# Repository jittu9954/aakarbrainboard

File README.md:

# AAKAR BRAINBOARD

Aakar Brainboard v2 is a modular CNC controller board based on LPC1768 Cortex-M3 chip. Due to its modular design it allows easier upgrades as per requirements and easy replacement if there is any broken part. It runs on open source Smoothie modular firmware and is targeted at 3D Printers, Laser cutters, CNC Mills, Pick and Place and other small or Mid size CNC machines.

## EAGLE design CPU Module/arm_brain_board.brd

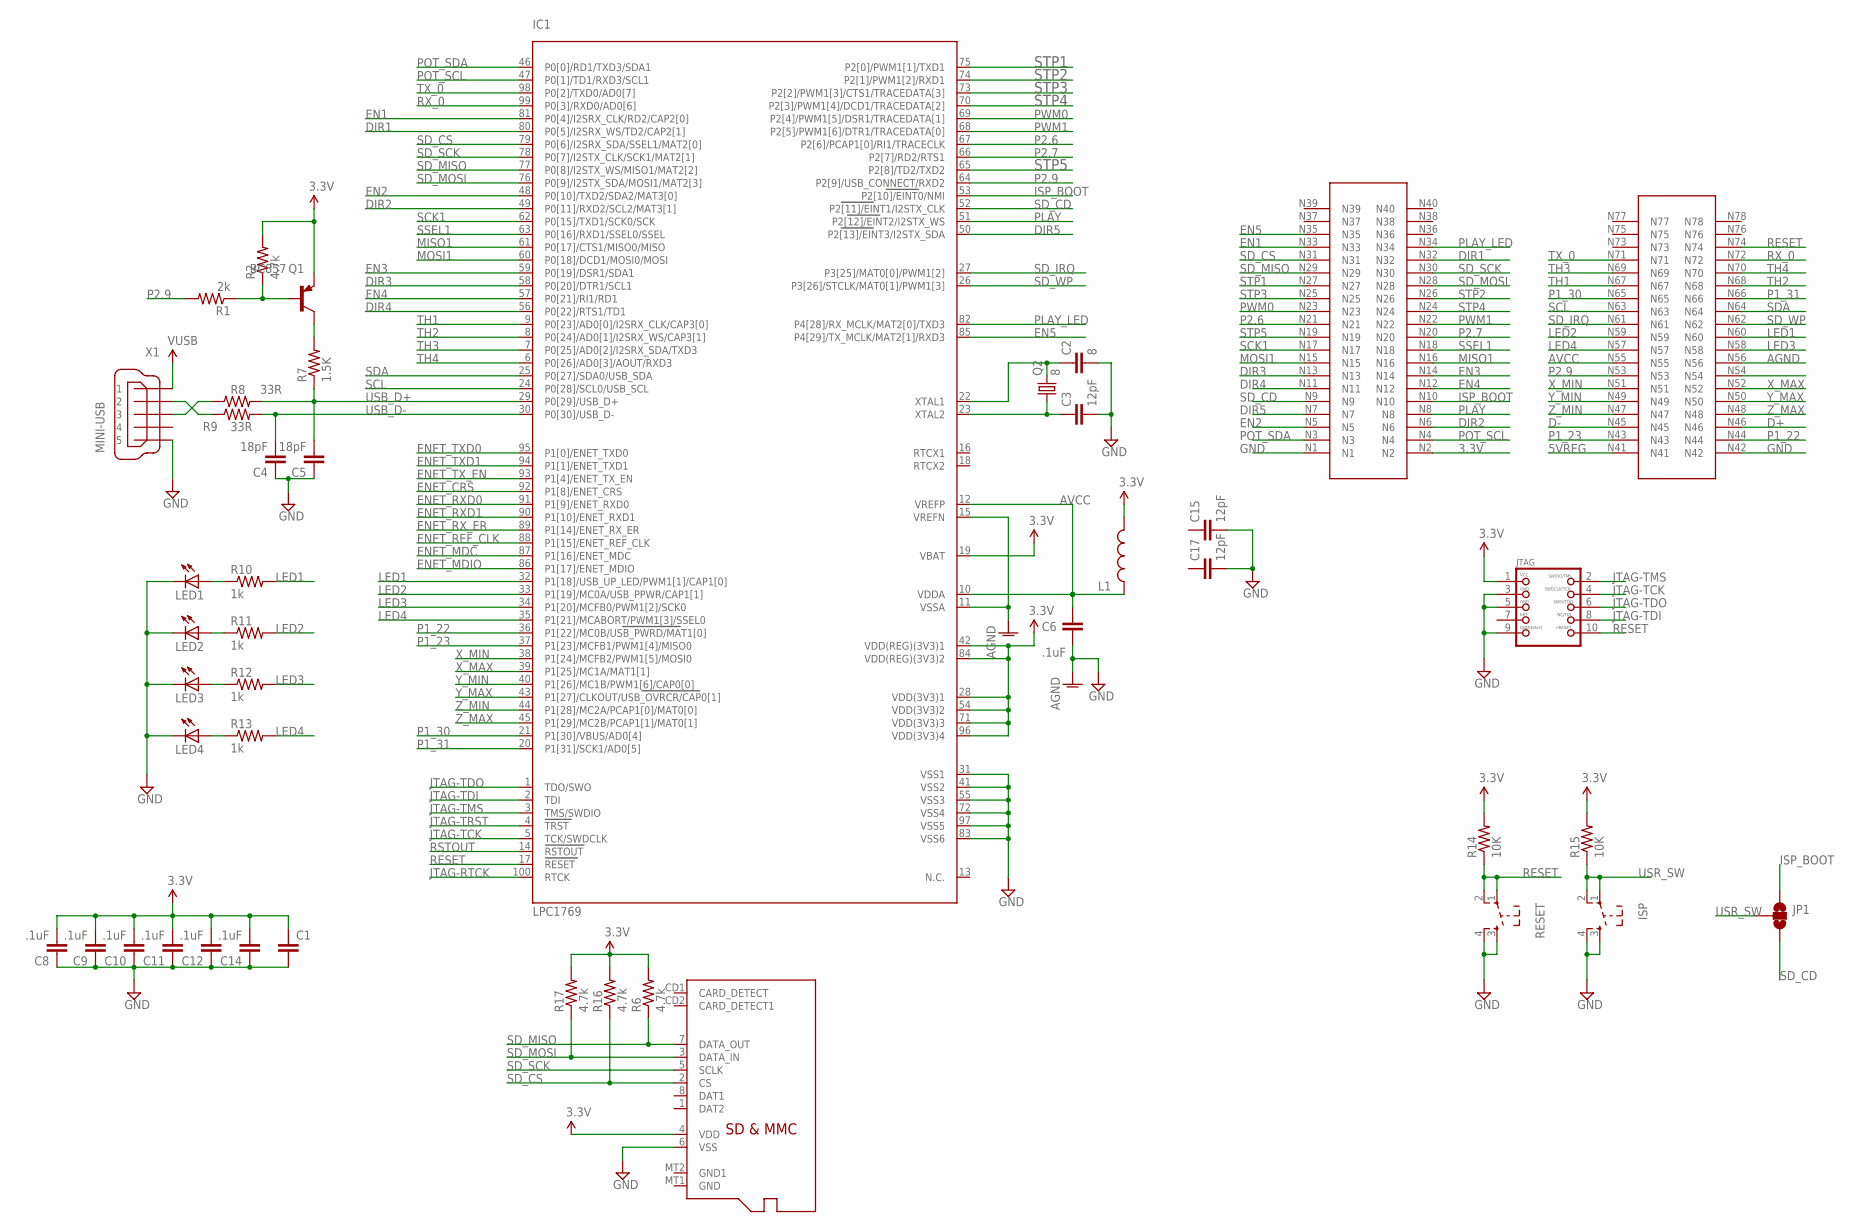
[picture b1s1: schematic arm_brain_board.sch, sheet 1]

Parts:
C1: CAP0603-CAP; 0603-CAP
C2: 8; 0603-CAP
C3, C15, C17: 12pF; 0603-CAP
C4: 18pF; 0603-CAP
C5: 18pF; C0603
C6, C8, C9, C10, C11, C12, C14: .1uF; 0603-CAP
IC1: LPC1769; LQFP100
ISP: SW_TACT_4P; SW_TACT_SMALL
JP1: SOLDERJUMPER_2WAYPASTE2&3; SJ_3_PASTE2&3
JTAG: JTAG-CORTEXM3; 2X05_1.27MM_SMT
L1: INDUCTOR0603; 0603
LED1, LED2, LED3, LED4: LEDCHIP-LED0603; CHIP-LED0603
MICROSD: MICROSD
Q1: BC857; SOT23-BEC
Q2: 8; HC49/S
R1: 2k; 0603-RES
R2: 4.7k; 0603-RES
R6, R16, R17: 4.7k; 0805
R7: 1.5K; 0603-RES
R8, R9: 33R; 0805
R10, R11, R12, R13: 1k; 0603-RES
R14, R15: 10K; 0603-RES
RESET: SW_TACT_4P; SW_TACT_SMALL
U$1: CPU_HEADER; CPU_BOARD
X1: MINI-USB; 32005-400

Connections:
3.3V: C1.1, C8.2, C9.2, C10.2, C11.2, C12.2, C14.2, IC1.19 (VBAT), IC1.28 (VDD(3V3)1), IC1.42 (VDD(REG)(3V3)1), IC1.54 (VDD(3V3)2), IC1.71 (VDD(3V3)3), IC1.84 (VDD(REG)(3V3)2), IC1.96 (VDD(3V3)4), JTAG.1, L1.2, MICROSD.4 (VDD), Q1.E, R2.2, R6.2, R14.2, R15.2, R16.2, R17.2, U$1.N2; also elsewhere on the board
5VREG: U$1.N41; also elsewhere on the board
AGND: C6.2, IC1.11 (VSSA), IC1.15 (VREFN), U$1.N56
AVCC: C6.1, IC1.10 (VDDA), IC1.12 (VREFP), L1.1, U$1.N55
D+: R8.1, U$1.N46, X1.3
D-: R9.1, U$1.N45, X1.2
DIR1: IC1.80 (P0[5]/I2SRX_WS/TD2/CAP2[1]), U$1.N32
DIR2: IC1.49 (P0[11]/RXD2/SCL2/MAT3[1]), U$1.N6
DIR3: IC1.58 (P0[20]/DTR1/SCL1), U$1.N13
DIR4: IC1.56 (P0[22]/RTS1/TD1), U$1.N11
DIR5: IC1.50 (P2[13]/EINT3/I2STX_SDA), U$1.N7
EN1: IC1.81 (P0[4]/I2SRX_CLK/RD2/CAP2[0]), U$1.N33
EN2: IC1.48 (P0[10]/TXD2/SDA2/MAT3[0]), U$1.N5
EN3: IC1.59 (P0[19]/DSR1/SDA1), U$1.N14
EN4: IC1.57 (P0[21]/RI1/RD1), U$1.N12
EN5: IC1.85 (P4[29]/TX_MCLK/MAT2[1]/RXD3), U$1.N35
ENET_CRS: IC1.92 (P1[8]/ENET_CRS); also elsewhere on the board
ENET_MDC: IC1.87 (P1[16]/ENET_MDC); also elsewhere on the board
ENET_MDIO: IC1.86 (P1[17]/ENET_MDIO); also elsewhere on the board
ENET_REF_CLK: IC1.88 (P1[15]/ENET_REF_CLK); also elsewhere on the board
ENET_RXD0: IC1.91 (P1[9]/ENET_RXD0); also elsewhere on the board
ENET_RXD1: IC1.90 (P1[10]/ENET_RXD1); also elsewhere on the board
ENET_RX_ER: IC1.89 (P1[14]/ENET_RX_ER); also elsewhere on the board
ENET_TXD0: IC1.95 (P1[0]/ENET_TXD0); also elsewhere on the board
ENET_TXD1: IC1.94 (P1[1]/ENET_TXD1); also elsewhere on the board
ENET_TX_EN: IC1.93 (P1[4]/ENET_TX_EN); also elsewhere on the board
GND: C1.2, C2.2, C3.2, C4.1, C5.1, C8.1, C9.1, C10.1, C11.1, C12.1, C14.1, C15.2, C17.2, IC1.31 (VSS1), IC1.41 (VSS2), IC1.55 (VSS3), IC1.72 (VSS4), IC1.83 (VSS6), IC1.97 (VSS5), ISP.3, ISP.4, JTAG.3, JTAG.5, JTAG.9, LED1.C, LED2.C, LED3.C, LED4.C, MICROSD.6 (VSS), RESET.3, RESET.4, U$1.N1, U$1.N42, X1.5; also elsewhere on the board
ISP_BOOT: IC1.53 (P2[10]/EINT0/NMI), JP1.1, U$1.N10
JTAG-RTCK: IC1.100 (RTCK)
JTAG-TCK: IC1.5 (TCK/SWDCLK), JTAG.4
JTAG-TDI: IC1.2 (TDI), JTAG.8
JTAG-TDO: IC1.1 (TDO/SWO), JTAG.6
JTAG-TMS: IC1.3 (TMS/SWDIO), JTAG.2
JTAG-TRST: IC1.4 (TRST)
LED1: IC1.32 (P1[18]/USB_UP_LED/PWM1[1]/CAP1[0]), R10.2, U$1.N60
LED2: IC1.33 (P1[19]/MC0A/USB_PPWR/CAP1[1]), R11.2, U$1.N59
LED3: IC1.34 (P1[20]/MCFB0/PWM1[2]/SCK0), R12.2, U$1.N58
LED4: IC1.35 (P1[21]/MCABORT/PWM1[3]/SSEL0), R13.2, U$1.N57
MISO1: IC1.61 (P0[17]/CTS1/MISO0/MISO), U$1.N16
MOSI1: IC1.60 (P0[18]/DCD1/MOSI0/MOSI), U$1.N15
unnamed: C2.1, IC1.22 (XTAL1), Q2.2
unnamed: C3.1, IC1.23 (XTAL2), Q2.1
unnamed: Q1.B, R1.1, R2.1
unnamed: Q1.C, R7.2
unnamed: LED4.A, R13.1
unnamed: LED3.A, R12.1
unnamed: LED2.A, R11.1
unnamed: LED1.A, R10.1
P1_22: IC1.36 (P1[22]/MC0B/USB_PWRD/MAT1[0]), U$1.N44
P1_23: IC1.37 (P1[23]/MCFB1/PWM1[4]/MISO0), U$1.N43
P1_30: IC1.21 (P1[30]/VBUS/AD0[4]), U$1.N65
P1_31: IC1.20 (P1[31]/SCK1/AD0[5]), U$1.N66
P2.6: IC1.67 (P2[6]/PCAP1[0]/RI1/TRACECLK), U$1.N21
P2.7: IC1.66 (P2[7]/RD2/RTS1), U$1.N20
P2.9: IC1.64 (P2[9]/USB_CONNECT/RXD2), R1.2, U$1.N53
PLAY: IC1.51 (P2[12]/EINT2/I2STX_WS), U$1.N8
PLAY_LED: IC1.82 (P4[28]/RX_MCLK/MAT2[0]/TXD3), U$1.N34
POT_SCL: IC1.47 (P0[1]/TD1/RXD3/SCL1), U$1.N4
POT_SDA: IC1.46 (P0[0]/RD1/TXD3/SDA1), U$1.N3
PWM0: IC1.69 (P2[4]/PWM1[5]/DSR1/TRACEDATA[1]), U$1.N23
PWM1: IC1.68 (P2[5]/PWM1[6]/DTR1/TRACEDATA[0]), U$1.N22
RESET: IC1.17 (RESET), JTAG.10, R14.1, RESET.1, RESET.2, U$1.N74
RSTOUT: IC1.14 (RSTOUT); also elsewhere on the board
RX_0: IC1.99 (P0[3]/RXD0/AD0[6]), U$1.N72
SCK1: IC1.62 (P0[15]/TXD1/SCK0/SCK), U$1.N17
SCL: IC1.24 (P0[28]/SCL0/USB_SCL), U$1.N63
SDA: IC1.25 (P0[27]/SDA0/USB_SDA), U$1.N64
SD_CD: IC1.52 (P2[11]/EINT1/I2STX_CLK), JP1.3, U$1.N9
SD_CS: IC1.79 (P0[6]/I2SRX_SDA/SSEL1/MAT2[0]), MICROSD.2 (CS), R16.1, U$1.N31
SD_IRQ: IC1.27 (P3[25]/MAT0[0]/PWM1[2]), U$1.N61
SD_MISO: IC1.77 (P0[8]/I2STX_WS/MISO1/MAT2[2]), MICROSD.7 (DATA_OUT), R6.1, U$1.N29
SD_MOSI: IC1.76 (P0[9]/I2STX_SDA/MOSI1/MAT2[3]), MICROSD.3 (DATA_IN), R17.1, U$1.N28
SD_SCK: IC1.78 (P0[7]/I2STX_CLK/SCK1/MAT2[1]), MICROSD.5 (SCLK), U$1.N30
SD_WP: IC1.26 (P3[26]/STCLK/MAT0[1]/PWM1[3]), U$1.N62
SSEL1: IC1.63 (P0[16]/RXD1/SSEL0/SSEL), U$1.N18
STP1: IC1.75 (P2[0]/PWM1[1]/TXD1), U$1.N27
STP2: IC1.74 (P2[1]/PWM1[2]/RXD1), U$1.N26
STP3: IC1.73 (P2[2]/PWM1[3]/CTS1/TRACEDATA[3]), U$1.N25
STP4: IC1.70 (P2[3]/PWM1[4]/DCD1/TRACEDATA[2]), U$1.N24
STP5: IC1.65 (P2[8]/TD2/TXD2), U$1.N19
TH1: IC1.9 (P0[23]/AD0[0]/I2SRX_CLK/CAP3[0]), U$1.N67
TH2: IC1.8 (P0[24]/AD0[1]/I2SRX_WS/CAP3[1]), U$1.N68
TH3: IC1.7 (P0[25]/AD0[2]/I2SRX_SDA/TXD3), U$1.N69
TH4: IC1.6 (P0[26]/AD0[3]/AOUT/RXD3), U$1.N70
TX_0: IC1.98 (P0[2]/TXD0/AD0[7]), U$1.N71
USB_D+: C5.2, IC1.29 (P0[29]/USB_D+), R7.1, R8.2
USB_D-: C4.2, IC1.30 (P0[30]/USB_D-), R9.2
USR_SW: ISP.1, ISP.2, JP1.2, R15.1
VUSB: X1.1; also elsewhere on the board
X_MAX: IC1.39 (P1[25]/MC1A/MAT1[1]), U$1.N52
X_MIN: IC1.38 (P1[24]/MCFB2/PWM1[5]/MOSI0), U$1.N51
Y_MAX: IC1.43 (P1[27]/CLKOUT/USB_OVRCR/CAP0[1]), U$1.N50
Y_MIN: IC1.40 (P1[26]/MC1B/PWM1[6]/CAP0[0]), U$1.N49
Z_MAX: IC1.45 (P1[29]/MC2B/PCAP1[1]/MAT0[1]), U$1.N48
Z_MIN: IC1.44 (P1[28]/MC2A/PCAP1[0]/MAT0[0]), U$1.N47

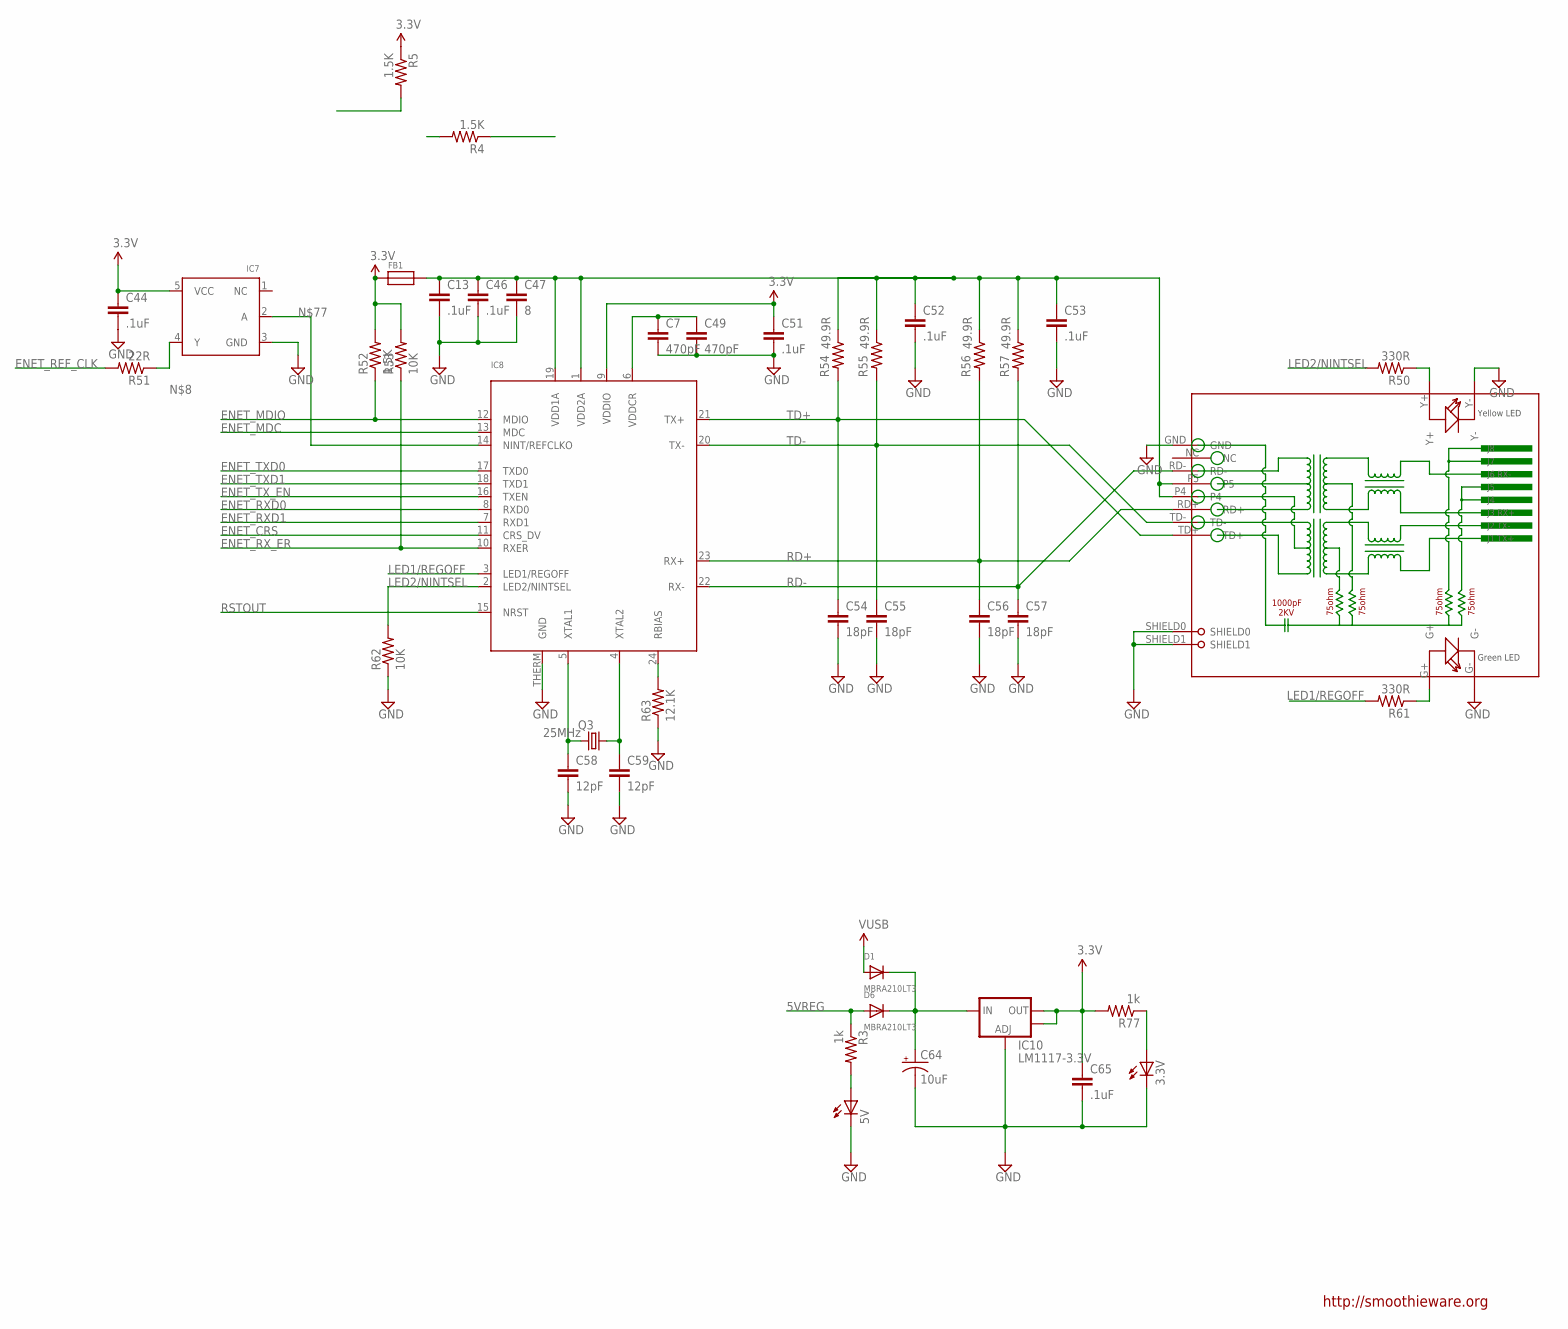
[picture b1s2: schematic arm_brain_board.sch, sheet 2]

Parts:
3.3V, 5V: LEDCHIP-LED0603; CHIP-LED0603
C7, C49: 470pF; 0603-CAP
C13, C44, C46, C51, C52, C53: .1uF; 0603-CAP
C47: 8; 0603-CAP
C54, C57: 18pF; 0805
C55, C56: 18pF; 0603-CAP
C58, C59: 12pF; 0603-CAP
C64: 10uF; EIA3216
C65: .1uF; 0805
D1, D6: MBRA210LT3; SOD-123
FB1: FERRITE; 0603
IC7: 74LVC1G04; SOT23-5
IC8: LAN8720; QFN24_4MM
IC10: LM1117-3.3V; SOT223
Q3: 25MHz; HC49/S
R3, R77: 1k; 0603-RES
R4, R5, R52: 1.5K; 0603-RES
R50, R61: 330R; R0603
R51: 22R; 0603-RES
R53, R62: 10K; 0603-RES
R54, R57: 49.9R; 0603-RES
R55, R56: 49.9R; 0805
R63: 12.1K; 0603-RES
RJ1: HR911105A

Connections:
3.3V: C44.1, C51.1, C65.1, FB1.1, IC7.5 (VCC), IC8.9 (VDDIO), IC10.2 (OUT), IC10.4 (OUT), R5.1, R52.2, R53.2, R77.2; also elsewhere on the board
5VREG: D6.A, R3.1; also elsewhere on the board
ENET_CRS: IC8.11 (CRS_DV); also elsewhere on the board
ENET_MDC: IC8.13 (MDC); also elsewhere on the board
ENET_MDIO: IC8.12 (MDIO), R52.1; also elsewhere on the board
ENET_REF_CLK: R51.2; also elsewhere on the board
ENET_RXD0: IC8.8 (RXD0); also elsewhere on the board
ENET_RXD1: IC8.7 (RXD1); also elsewhere on the board
ENET_RX_ER: IC8.10 (RXER), R53.1; also elsewhere on the board
ENET_TXD0: IC8.17 (TXD0); also elsewhere on the board
ENET_TXD1: IC8.18 (TXD1); also elsewhere on the board
ENET_TX_EN: IC8.16 (TXEN); also elsewhere on the board
GND: 3.3V.C, 5V.C, C7.2, C13.2, C44.2, C46.2, C47.2, C49.2, C51.2, C52.2, C53.2, C54.2, C55.2, C56.2, C57.2, C58.2, C59.2, C64.C (-), C65.2, IC7.3 (GND), IC8.THERM (GND), IC10.1 (ADJ), R62.1, R63.1, RJ1.G-, RJ1.GND, RJ1.SHIELD0, RJ1.SHIELD1, RJ1.Y-; also elsewhere on the board
LED1/REGOFF: IC8.3 (LED1/REGOFF), R61.2
LED2/NINTSEL: IC8.2 (LED2/NINTSEL), R50.2, R62.2
unnamed: C64.A (+), D1.C, D6.C, IC10.3 (IN)
unnamed: R50.1, RJ1.Y+
unnamed: R61.1, RJ1.G+
unnamed: IC7.4 (Y), R5.2, R51.1
unnamed: 5V.A, R3.2
unnamed: C13.1, C46.1, C47.1, C52.1, C53.1, FB1.2, IC8.1 (VDD2A), IC8.19 (VDD1A), R54.1, R55.1, R56.1, R57.1, RJ1.P4, RJ1.P5
unnamed: C59.1, IC8.4 (XTAL2), Q3.1
unnamed: C58.1, IC8.5 (XTAL1), Q3.2
unnamed: IC8.24 (RBIAS), R63.2
unnamed: IC7.2 (A), IC8.14 (NINT/REFCLKO), R4.1
unnamed: 3.3V.A, R77.1
unnamed: C7.1, C49.1, IC8.6 (VDDCR)
RD+: C56.1, IC8.23 (RX+), R56.2, RJ1.RD+
RD-: C57.1, IC8.22 (RX-), R57.2, RJ1.RD-
RSTOUT: IC8.15 (NRST); also elsewhere on the board
TD+: C54.1, IC8.21 (TX+), R54.2, RJ1.TD+
TD-: C55.1, IC8.20 (TX-), R55.2, RJ1.TD-
VUSB: D1.A; also elsewhere on the board

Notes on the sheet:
http://smoothieware.org

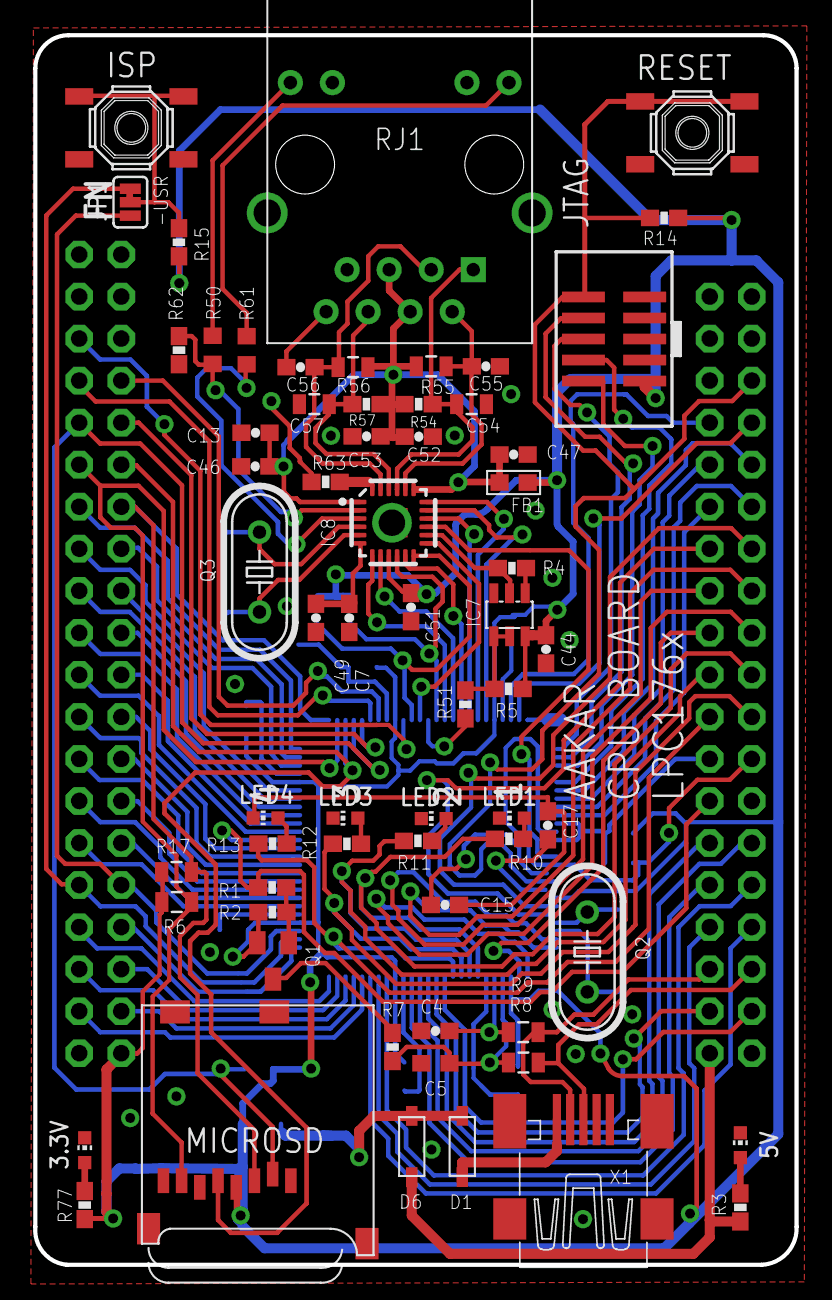
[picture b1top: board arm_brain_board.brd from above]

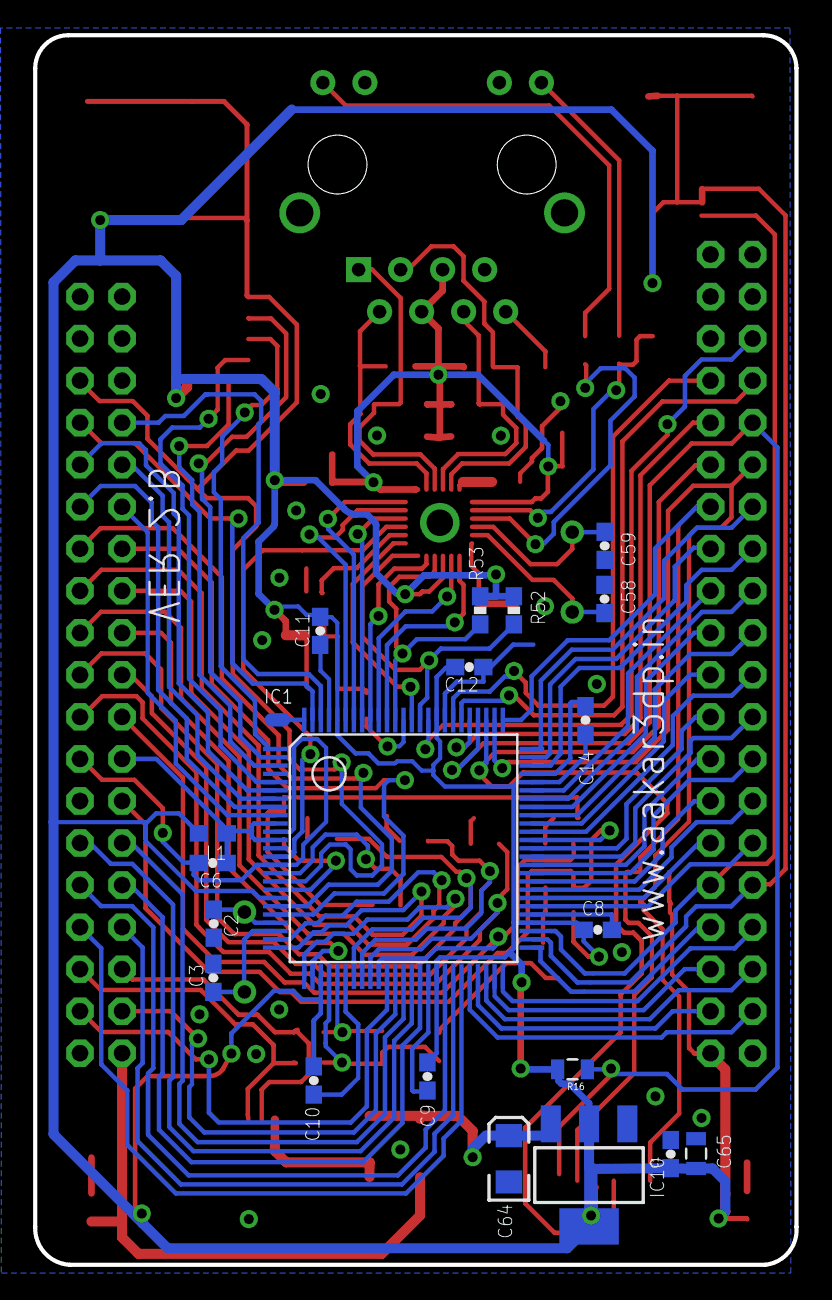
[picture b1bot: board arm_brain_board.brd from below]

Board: 2 copper layers, 46.0 x 74.3 mm, 85 parts (20 on the bottom side), 111 nets.

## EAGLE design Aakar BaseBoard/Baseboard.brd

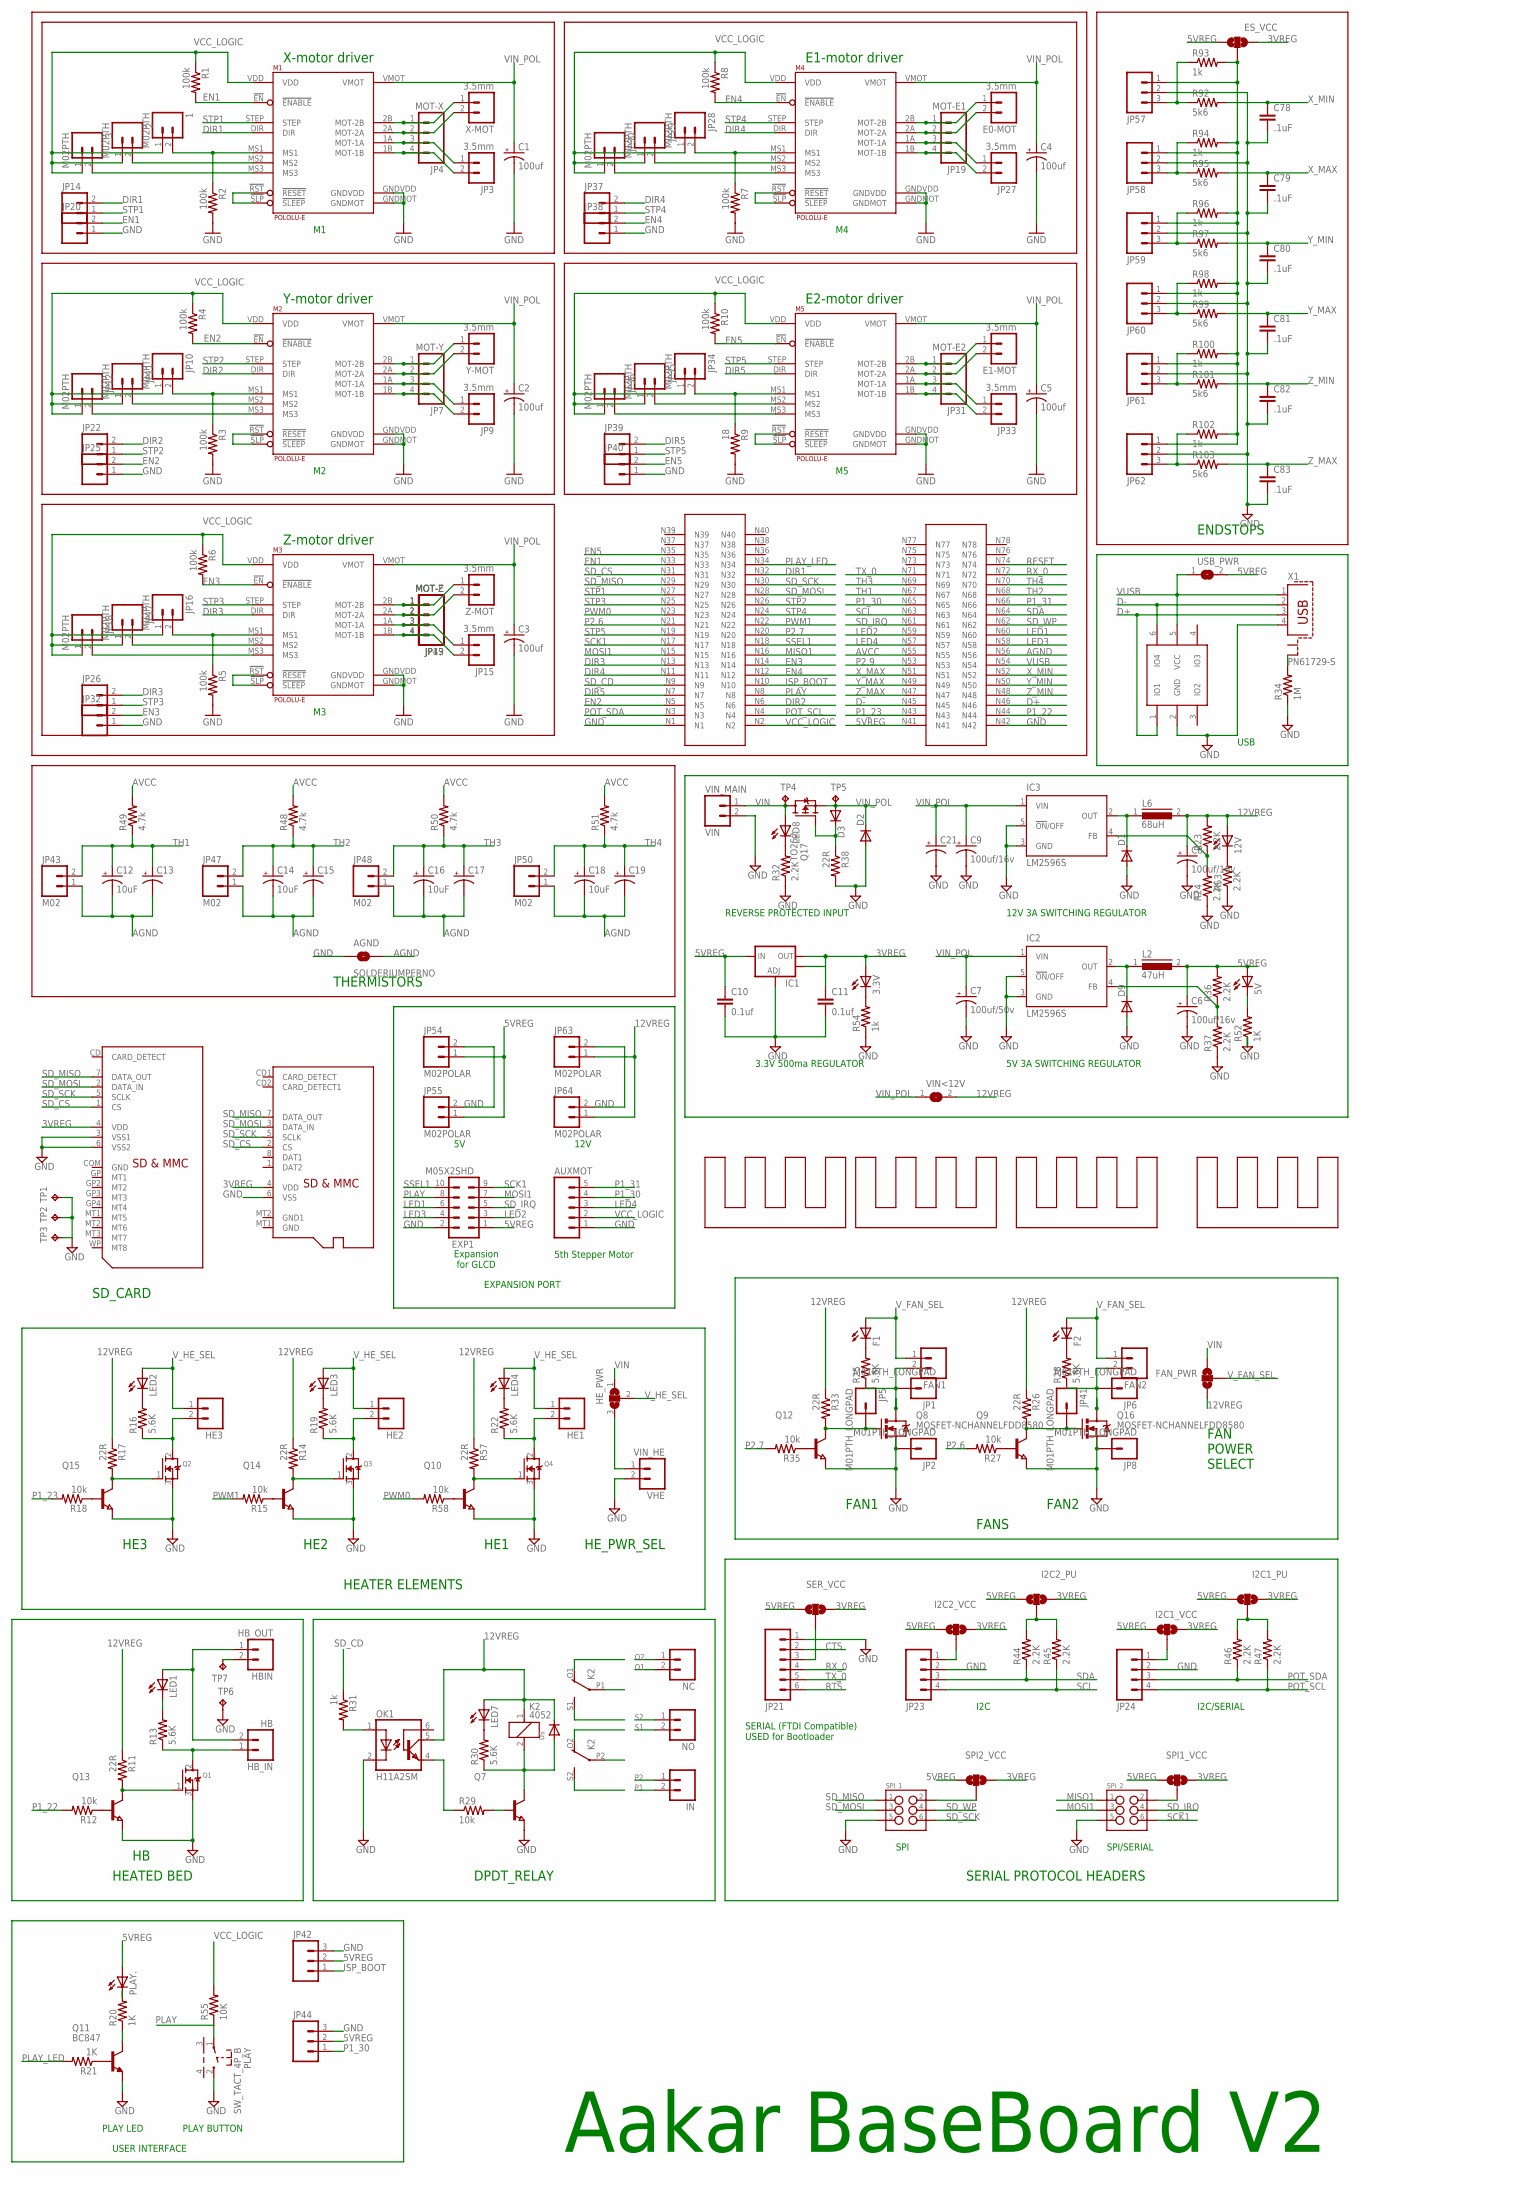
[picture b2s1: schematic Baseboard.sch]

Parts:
1, 2, 3: M02PTH; 1X02
3.3V, 5V, 12V: LEDCHIP-LED0603; CHIP-LED0603
AGND: SOLDERJUMPERNO; SJ_2S-NO
AUXMOT: M05PTH_LONGPADS; 1X05_LONGPADS
C1, C2, C3, C4, C5: 100uf; CPOL-RADIAL-100UF-25V
C6, C8, C9: 100uf/16v; E3,5-8
C7: 100uf/50v; E5-10,5
C10, C11: 0.1uf; 0805
C12, C14, C16, C18: 10uF; EIA3216
C13, C15, C17, C19: CAP_POLPTH2; CPOL-RADIAL-10UF-25V
C21: CPOL-USE2.5-7; E2,5-7
C78, C79, C80, C81, C82, C83: .1uF; 0805
D1, D9: DIODE-SMC; SMC
D2, D3: DIODE-GF1; GF1
D5: DIODESMA; SMADIODE
E0-MOT, E1-MOT: 3.5mm; SCREWTERMINAL-3.5MM-2_LOCK
ES_VCC: SOLDERJUMPER_2WAYS; SJ_3
EXP1: M05X2SHD; 2X5-SHROUDED
F1, F2: LEDCHIP-LED0603; CHIP-LED0603
FAN1, FAN2: M025MM; SCREWTERMINAL-5MM-2
FAN_PWR: SOLDERJUMPER_2WAYT; SJ_2
HB: HB_IN; SCREWTERMINAL-5MM-2
HBIN: HB_OUT; SCREWTERMINAL-5MM-2
HE1, HE2, HE3: M025MM; SCREWTERMINAL-5MM-2
HE_PWR: SJ2WW; SJ_2W
I2C1_PU, I2C1_VCC, I2C2_PU, I2C2_VCC: SOLDERJUMPER_2WAYPASTE1&2; SJ_3_PASTE1&2
IC1: V_REG_LM1117SOT223; SOT223
IC2, IC3: LM2596S; TO263-5
IN: M025MM; SCREWTERMINAL-5MM-2
JP1, JP2, JP5, JP6, JP8, JP41: M01PTH_LONGPAD; 1X01_LONGPAD
JP3, JP9, JP15, JP27, JP33: 3.5mm; SCREWTERMINAL-3.5MM-2_LOCK
JP4: MOT-X; MOLEX-1X4
JP7: MOT-Y; MOLEX-1X4
JP10, JP11, JP12, JP16, JP17, JP18, JP28, JP29, JP30, JP34, JP35, JP36: M02PTH; 1X02
JP13: MOT-E; MOLEX-1X4
JP14, JP20, JP22, JP25, JP26, JP32, JP37, JP38, JP39, JP40: M02POGO_PIN_HOLES_ONLY; 1X02_PP_HOLES_ONLY
JP19: MOT-E1; MOLEX-1X4
JP21: M06POLAR; MOLEX-1X6
JP23, JP24: M04POLAR; MOLEX-1X4
JP31: MOT-E2; MOLEX-1X4
JP42, JP44, JP57, JP58, JP59, JP60, JP61, JP62: M03POLAR; MOLEX-1X3
JP43, JP47, JP48, JP50: M02; MOLEX-1X2_LOCK
JP49: MOT-Z; MOLEX-1X4
JP54, JP55, JP63, JP64: M02POLAR; MOLEX-1X2
K2: 4052; F4052
L2: 47uH; A26GFC
L6: 68uH; A26GFC
LED1, LED2, LED3, LED4, LED7, LED8: LEDCHIP-LED0603; CHIP-LED0603
M1, M2, M3, M4, M5: POLOLU-E; POLOLU-ALLEGRO-PTH
NC: M025MM; SCREWTERMINAL-5MM-2
NO: M025MM; SCREWTERMINAL-5MM-2
OK1: H11A2SM; DIL6-SMD
PLAY: SW_TACT_4P_B; SW_TACT_STANDARD_RIGHT_ANGLE
PLAY.: LED5MM
Q1, Q2, Q3, Q4: MOSFET-NGDS_TO220V; TO220V
Q7, Q9, Q10, Q12, Q13, Q14, Q15: NPN-TRANSISTOR_SOT23; SOT23
Q8, Q16: MOSFET-NCHANNELFDD8580; DPAK
Q11: BC847; SOT23
Q17: TO252
R1, R2, R3, R4, R5, R6, R7, R8, R10: 100k; 0603-RES
R9: 18; 0603-RES
R11, R14, R17, R26, R33, R38, R57: 22R; 0603-RES
R12, R15, R18, R27, R29, R35, R58: 10k; 0603-RES
R13, R16, R19, R22, R25, R28, R30: 5.6K; 0603-RES
R20, R21, R52: 1K; 0603-RES
R23, R24, R32, R36, R37, R44, R45, R46, R47, R53: 2.2K; 0603-RES
R31, R54, R93, R94, R96, R98, R100, R102: 1k; 0603-RES
R34: 1M; 0805
R48, R49, R50, R51: 4.7k; 0603-RES
R55: 10K; 0603-RES
R92, R95, R97, R99, R101, R103: 5k6; 0603-RES
SER_VCC: SOLDERJUMPER_2WAYPASTE1&2; SJ_3_PASTE1&2
SPI1_VCC, SPI2_VCC: SOLDERJUMPER_2WAYPASTE1&2; SJ_3_PASTE1&2
SPI_1, SPI_2: M03X2NO_SILK; 2X3-NS
TP1, TP2, TP3: TPTP15SQ; TP15SQ
TP4, TP5: TPPAD1-13; P1-13
TP6, TP7: TPPAD1-17Y; P1-17Y
U$1, U$8, U$10, U$12: HEATSINK; HEAT_TO
U$2: MICROSD
U$4: CPU_HEADER; CPU_BOARD
U$9: ESD; SOT23-6
U$11: SD_MMC
USB_PWR: SJ
VHE: VIN_HE; SCREWTERMINAL-5MM-2
VIN: VIN_MAIN; SCREWTERMINAL-5MM-2
VIN<12V: SJ
X1: PN61729-S
X-MOT: 3.5mm; SCREWTERMINAL-3.5MM-2_LOCK
Y-MOT: 3.5mm; SCREWTERMINAL-3.5MM-2_LOCK
Z-MOT: 3.5mm; SCREWTERMINAL-3.5MM-2_LOCK

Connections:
3VREG: 3.3V.A, C11.1, ES_VCC.3, I2C1_PU.3, I2C1_VCC.3, I2C2_PU.3, I2C2_VCC.3, IC1.2 (OUT), IC1.4 (OUT), SER_VCC.3, SPI1_VCC.3, SPI2_VCC.3, U$2.4 (VDD), U$11.4 (VDD)
5VREG: 5V.A, C6.+, C10.1, ES_VCC.1, EXP1.1, I2C1_PU.1, I2C1_VCC.1, I2C2_PU.1, I2C2_VCC.1, IC1.3 (IN), JP42.2, JP44.2, JP54.1, JP55.1, L2.2, PLAY..A, R36.2, SER_VCC.1, SPI1_VCC.1, SPI2_VCC.1, U$4.N41, USB_PWR.2
12VREG: 12V.A, C8.+, D5.C, FAN_PWR.3, JP63.1, JP64.1, K2.1, L6.2, LED7.A, OK1.5 (COL), R11.1, R14.1, R17.1, R23.2, R26.1, R33.1, R57.1, VIN<12V.2
AGND: AGND.2, C12.C (-), C13.2 (-), C14.C (-), C15.2 (-), C16.C (-), C17.2 (-), C18.C (-), C19.2 (-), JP43.1, JP47.1, JP48.1, JP50.1, U$4.N56
AVCC: R48.2, R49.2, R50.2, R51.2, U$4.N55
CTS: JP21.2
D+: U$4.N46, U$9.1 (IO1), X1.3
D-: U$4.N45, U$9.6 (IO4), X1.2
DIR1: JP14.2, M1.DIR, U$4.N32
DIR2: JP22.2, M2.DIR, U$4.N6
DIR3: JP26.2, M3.DIR, U$4.N13
DIR4: JP37.2, M4.DIR, U$4.N11
DIR5: JP39.2, M5.DIR, U$4.N7
E-MOT-1A: JP3.1, JP4.3, M1.1A (MOT-1A)
E-MOT-1A1: JP7.3, JP9.1, M2.1A (MOT-1A)
E-MOT-1A2: JP13.3, JP15.1, JP49.3, M3.1A (MOT-1A)
E-MOT-1A3: JP19.3, JP27.1, M4.1A (MOT-1A)
E-MOT-1A4: JP31.3, JP33.1, M5.1A (MOT-1A)
E-MOT-1B: JP3.2, JP4.4, M1.1B (MOT-1B)
E-MOT-1B1: JP7.4, JP9.2, M2.1B (MOT-1B)
E-MOT-1B2: JP13.4, JP15.2, JP49.4, M3.1B (MOT-1B)
E-MOT-1B3: JP19.4, JP27.2, M4.1B (MOT-1B)
E-MOT-1B4: JP31.4, JP33.2, M5.1B (MOT-1B)
E-MOT-2A: JP4.2, M1.2A (MOT-2A), X-MOT.2
E-MOT-2A1: JP7.2, M2.2A (MOT-2A), Y-MOT.2
E-MOT-2A2: JP13.2, JP49.2, M3.2A (MOT-2A), Z-MOT.2
E-MOT-2A3: E0-MOT.2, JP19.2, M4.2A (MOT-2A)
E-MOT-2A4: E1-MOT.2, JP31.2, M5.2A (MOT-2A)
E-MOT-2B: JP4.1, M1.2B (MOT-2B), X-MOT.1
E-MOT-2B1: JP7.1, M2.2B (MOT-2B), Y-MOT.1
E-MOT-2B2: JP13.1, JP49.1, M3.2B (MOT-2B), Z-MOT.1
E-MOT-2B3: E0-MOT.1, JP19.1, M4.2B (MOT-2B)
E-MOT-2B4: E1-MOT.1, JP31.1, M5.2B (MOT-2B)
E-RESETSLEEP: M1.!RST (!RESET), M1.!SLP (!SLEEP)
E-RESETSLEEP1: M2.!RST (!RESET), M2.!SLP (!SLEEP)
E-RESETSLEEP2: M3.!RST (!RESET), M3.!SLP (!SLEEP)
E-RESETSLEEP3: M4.!RST (!RESET), M4.!SLP (!SLEEP)
E-RESETSLEEP4: M5.!RST (!RESET), M5.!SLP (!SLEEP)
EN1: JP20.2, M1.!EN (!ENABLE), R1.2, U$4.N33
EN2: JP25.2, M2.!EN (!ENABLE), R4.2, U$4.N5
EN3: JP32.2, M3.!EN (!ENABLE), R6.2, U$4.N14
EN4: JP38.2, M4.!EN (!ENABLE), R8.2, U$4.N12
EN5: JP40.2, M5.!EN (!ENABLE), R10.2, U$4.N35
GND: AGND.1, AUXMOT.1, C1.2 (-), C2.2 (-), C3.2 (-), C4.2 (-), C5.2 (-), C6.-, C7.-, C8.-, C9.-, C10.2, C11.2, C21.-, C78.2, C79.2, C80.2, C81.2, C82.2, C83.2, D1.A, D2.A, D9.A, EXP1.2, IC1.1 (ADJ), IC2.3 (GND), IC2.5 (!ON!/OFF), IC3.3 (GND), IC3.5 (!ON!/OFF), JP2.1, JP8.1, JP20.1, JP21.1, JP23.2, JP24.2, JP25.1, JP32.1, JP38.1, JP40.1, JP42.3, JP44.3, JP54.2, JP55.2, JP57.2, JP58.2, JP59.2, JP60.2, JP61.2, JP62.2, JP63.2, JP64.2, M1.GNDMOT, M1.GNDVDD, M2.GNDMOT, M2.GNDVDD, M3.GNDMOT, M3.GNDVDD, M4.GNDMOT, M4.GNDVDD, M5.GNDMOT, M5.GNDVDD, OK1.2 (C), PLAY.2, Q1.3 (S), Q2.3 (S), Q3.3 (S), Q4.3 (S), Q7.2 (E), Q8.3 (S), Q9.2 (E), Q10.2 (E), Q11.2 (E), Q12.2 (E), Q13.2 (E), Q14.2 (E), Q15.2 (E), Q16.3 (S), R2.2, R3.2, R5.2, R7.2, R9.2, R24.1, R32.1, R34.1, R37.1, R38.2, R52.1, R53.1, R54.1, SPI_1.5, SPI_2.5, TP1.TP, TP2.TP, TP3.TP, TP6.TP, U$2.6 (VSS), U$4.N1, U$4.N42, U$9.2 (GND), U$11.3 (VSS1), U$11.6 (VSS2), VHE.2, VIN.2, X1.4
ISP_BOOT: JP42.1, U$4.N10
LED1: EXP1.6, U$4.N60
LED2: EXP1.3, U$4.N59
LED3: EXP1.4, U$4.N58
LED4: AUXMOT.3, U$4.N57
MISO1: SPI_2.1, U$4.N16
MOSI1: EXP1.7, SPI_2.3, U$4.N15
unnamed: JP11.2, M2.MS2
unnamed: JP10.2, M2.MS1, R3.1
unnamed: JP12.2, M2.MS3
unnamed: JP17.2, M3.MS2
unnamed: JP16.2, M3.MS1, R5.1
unnamed: JP18.2, M3.MS3
unnamed: JP29.2, M4.MS2
unnamed: JP28.2, M4.MS1, R7.1
unnamed: JP30.2, M4.MS3
unnamed: JP35.2, M5.MS2
unnamed: JP34.2, M5.MS1, R9.1
unnamed: JP36.2, M5.MS3
unnamed: D1.C, IC3.2 (OUT), L6.1
unnamed: D9.C, IC2.2 (OUT), L2.1
unnamed: HB.1, Q1.2 (D), R13.1
unnamed: HBIN.2, TP7.TP
unnamed: HB.2, HBIN.1, LED1.A
unnamed: Q1.1 (G), Q13.3 (C), R11.2
unnamed: LED1.C, R13.2
unnamed: 2.2, M1.MS2
unnamed: 1.2, M1.MS1, R2.1
unnamed: 3.2, M1.MS3
unnamed: SPI1_VCC.2, SPI_2.2
unnamed: LED2.C, R16.2
unnamed: SPI2_VCC.2, SPI_1.2
unnamed: Q3.1 (G), Q14.3 (C), R14.2
unnamed: HE3.2, Q2.2 (D), R16.1
unnamed: F1.C, R25.2
unnamed: LED3.C, R19.2
unnamed: Q14.1 (B), R15.1
unnamed: HE2.2, Q3.2 (D), R19.1
unnamed: Q13.1 (B), R12.1
unnamed: LED4.C, R22.2
unnamed: Q11.1 (B), R21.1
unnamed: HE1.2, Q4.2 (D), R22.1
unnamed: 5V.C, R52.2
unnamed: Q2.1 (G), Q15.3 (C), R17.2
unnamed: FAN1.2, JP1.1, Q8.4 (D), R25.1
unnamed: 12V.C, R53.2
unnamed: F2.C, R28.2
unnamed: JP41.1, Q9.3 (C), Q16.1 (G), R26.2
unnamed: FAN2.2, JP6.1, Q16.4 (D), R28.1
unnamed: 3.3V.C, R54.2
unnamed: OK1.1 (A), R31.2
unnamed: OK1.4 (EMI), R29.1
unnamed: Q7.1 (B), R29.2
unnamed: Q15.1 (B), R18.1
unnamed: LED7.C, R30.2
unnamed: D5.A, K2.2, Q7.3 (C), R30.1
unnamed: LED8.C, R32.2
unnamed: JP5.1, Q8.1 (G), Q12.3 (C), R33.2
unnamed: IC2.4 (FB), R36.1, R37.2
unnamed: JP21.3, SER_VCC.2
unnamed: R34.2, X1.S2
unnamed: PLAY..K (C), R20.2
unnamed: Q12.1 (B), R35.1
unnamed: I2C2_VCC.2, JP23.1
unnamed: I2C2_PU.2, R44.2, R45.2
unnamed: I2C1_VCC.2, JP24.1
unnamed: I2C1_PU.2, R46.2, R47.2
unnamed: D3.C, Q17.1 (G), R38.1
unnamed: JP61.3, R100.1, R101.1
unnamed: JP59.3, R96.1, R97.1
unnamed: JP62.3, R102.1, R103.1
unnamed: Q9.1 (B), R27.1
unnamed: Q4.1 (G), Q10.3 (C), R57.2
unnamed: Q10.1 (B), R58.1
unnamed: IC3.4 (FB), R23.1, R24.2
unnamed: JP58.3, R94.1, R95.1
unnamed: ES_VCC.2, JP57.1, JP58.1, JP59.1, JP60.1, JP61.1, JP62.1, R93.2, R94.2, R96.2, R98.2, R100.2, R102.2
unnamed: JP60.3, R98.1, R99.1
unnamed: JP57.3, R92.1, R93.1
O1: K2.O1 (O), NC.2
O2: K2.O2 (O), NC.1
P1: IN.2, K2.P1
P1_22: R12.2, U$4.N44
P1_23: R18.2, U$4.N43
P1_30: AUXMOT.4, JP44.1, U$4.N65
P1_31: AUXMOT.5, U$4.N66
P2: IN.1, K2.P2
P2.6: R27.2, U$4.N21
P2.7: R35.2, U$4.N20
P2.9: U$4.N53
PL#: Q11.3 (C), R20.1
PLAY: EXP1.8, PLAY.1, R55.1, U$4.N8
PLAY_LED: R21.2, U$4.N34
POT_SCL: JP24.4, R47.1, U$4.N4
POT_SDA: JP24.3, R46.1, U$4.N3
PWM0: R58.2, U$4.N23
PWM1: R15.2, U$4.N22
RESET: U$4.N74
RTS: JP21.6
RX_0: JP21.4, U$4.N72
S1: K2.S1 (S), NO.2
S2: K2.S2 (S), NO.1
SCK1: EXP1.9, SPI_2.6, U$4.N17
SCL: JP23.4, R45.1, U$4.N63
SDA: JP23.3, R44.1, U$4.N64
SD_CD: R31.1, U$4.N9
SD_CS: U$2.2 (CS), U$4.N31, U$11.1 (CS)
SD_IRQ: EXP1.5, SPI_2.4, U$4.N61
SD_MISO: SPI_1.1, U$2.7 (DATA_OUT), U$4.N29, U$11.7 (DATA_OUT)
SD_MOSI: SPI_1.3, U$2.3 (DATA_IN), U$4.N28, U$11.2 (DATA_IN)
SD_SCK: SPI_1.6, U$2.5 (SCLK), U$4.N30, U$11.5 (SCLK)
SD_WP: SPI_1.4, U$4.N62
SSEL1: EXP1.10, U$4.N18
STP1: JP14.1, M1.STEP, U$4.N27
STP2: JP22.1, M2.STEP, U$4.N26
STP3: JP26.1, M3.STEP, U$4.N25
STP4: JP37.1, M4.STEP, U$4.N24
STP5: JP39.1, M5.STEP, U$4.N19
TH1: C12.A (+), C13.1 (+), JP43.2, R49.1, U$4.N67
TH2: C14.A (+), C15.1 (+), JP47.2, R48.1, U$4.N68
TH3: C16.A (+), C17.1 (+), JP48.2, R50.1, U$4.N69
TH4: C18.A (+), C19.1 (+), JP50.2, R51.1, U$4.N70
TX_0: JP21.5, U$4.N71
VCC_LOGIC: 1.1, 2.1, 3.1, AUXMOT.2, JP10.1, JP11.1, JP12.1, JP16.1, JP17.1, JP18.1, JP28.1, JP29.1, JP30.1, JP34.1, JP35.1, JP36.1, M1.VDD, M2.VDD, M3.VDD, M4.VDD, M5.VDD, R1.1, R4.1, R6.1, R8.1, R10.1, R55.2, U$4.N2
VIN: FAN_PWR.1, HE_PWR.1, LED8.A, Q17.3 (D), TP4.TP, VIN.1
VIN_HE: HE_PWR.3, VHE.1
VIN_POL: C1.1 (+), C2.1 (+), C3.1 (+), C4.1 (+), C5.1 (+), C7.+, C9.+, C21.+, D2.C, D3.A, IC2.1 (VIN), IC3.1 (VIN), M1.VMOT, M2.VMOT, M3.VMOT, M4.VMOT, M5.VMOT, Q17.2 (S), TP5.TP, VIN<12V.1
VUSB: U$4.N54, U$9.5 (VCC), USB_PWR.1, X1.1
V_FAN_SEL: F1.A, F2.A, FAN1.1, FAN2.1, FAN_PWR.2
V_HE_SEL: HE1.1, HE2.1, HE3.1, HE_PWR.2, LED2.A, LED3.A, LED4.A
X_MAX: C79.1, R95.2, U$4.N51
X_MIN: C78.1, R92.2, U$4.N52
Y_MAX: C81.1, R99.2, U$4.N49
Y_MIN: C80.1, R97.2, U$4.N50
Z_MAX: C83.1, R103.2, U$4.N47
Z_MIN: C82.1, R101.2, U$4.N48

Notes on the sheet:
X-motor driver
Y-motor driver
Z-motor driver
E1-motor driver
E2-motor driver
SERIAL (FTDI Compatible) USED for Bootloader
I2C
I2C/SERIAL
SPI
SPI/SERIAL
5th Stepper Motor
SD_CARD
HE3
HE2
HE1
HE_PWR_SEL
DPDT_RELAY
HEATER ELEMENTS
HEATED BED
FAN1
FAN2
FAN POWER SELECT
FANS
THERMISTORS
ENDSTOPS
SERIAL PROTOCOL HEADERS
Expansion for GLCD
12V
PLAY LED
PLAY BUTTON
12V 3A SWITCHING REGULATOR
5V 3A SWITCHING REGULATOR
3.3V 500ma REGULATOR
REVERSE PROTECTED INPUT
USER INTERFACE
EXPANSION PORT
USB
Aakar BaseBoard V2

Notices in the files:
parts and their libraries:
SparkFun-Connectors: Licensing: CC v3.0 Share-Alike You are welcome to use this library for commercial purposes.
